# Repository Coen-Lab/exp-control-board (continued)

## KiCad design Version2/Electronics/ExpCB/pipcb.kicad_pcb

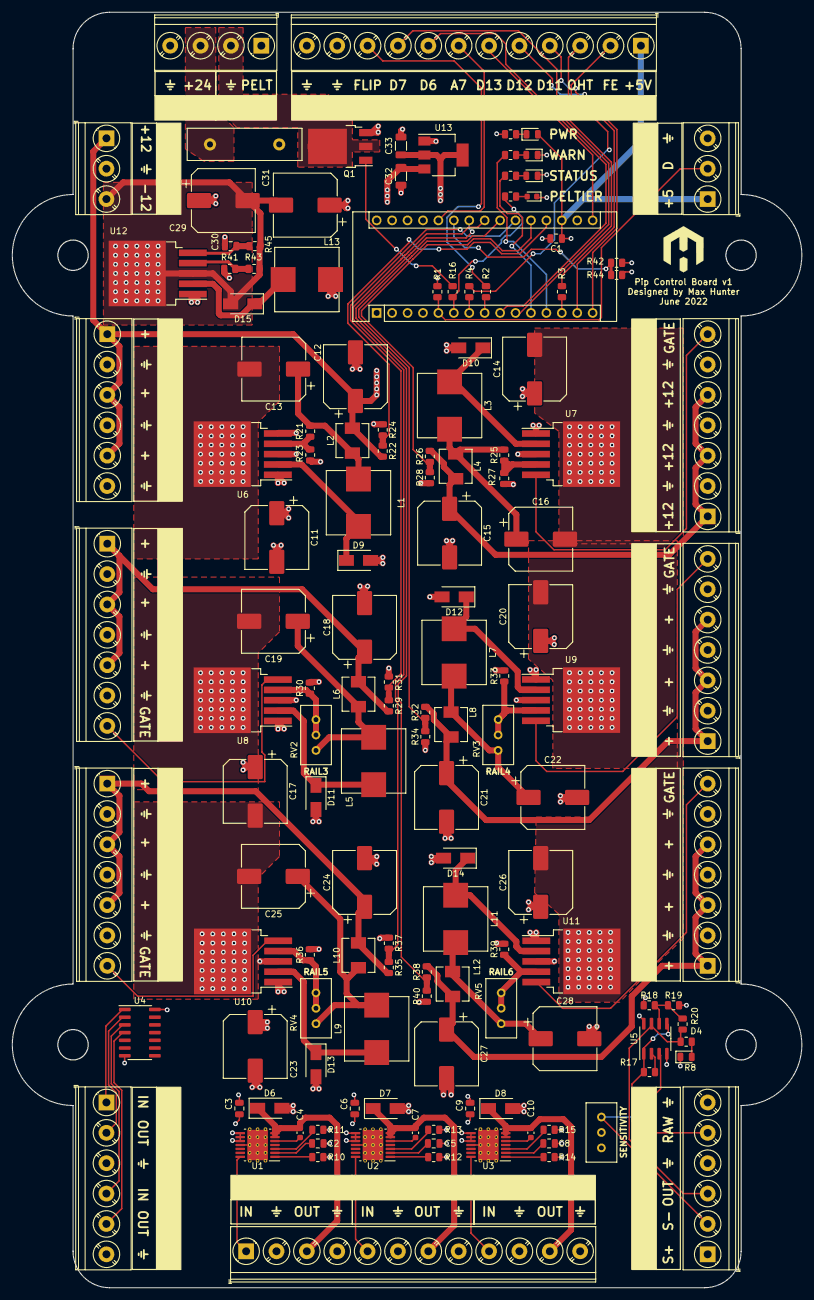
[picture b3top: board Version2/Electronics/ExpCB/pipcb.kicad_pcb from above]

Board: 4 copper layers, 130.0 x 210.0 mm, 140 parts (0 on the bottom side), 94 nets.

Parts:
A1: Arduino_Nano_v3.x; Arduino_Nano
C1, C30: 100n; C_0805_2012Metric
C2, C5, C8: 150n; C_0805_2012Metric
C3, C6, C9: 1u; C_0805_2012Metric
C4, C7, C10: 470p; C_0603_1608Metric
C11, C12, C13, C14, C15, C16, C17, C18, C19, C20, C21, C22, C23, C24, C25, C26, C27, C28, C29, C31: 220u; CP_Elec_10x10
C32, C33: 10u; C_1206_3216Metric
D1, D4: GREEN; LED_0805_2012Metric
D2: RED; LED_0805_2012Metric
D3: YELLOW; LED_0805_2012Metric
D5: BLUE; LED_0603_1608Metric
D6, D7, D8, D9, D10, D11, D12, D13, D14, D15: SS34; D_SMA
F1: 10A; Fuse_Littelfuse-LVR100
J1: 24V; TerminalBlock_Phoenix_PT-1,5-4-5.0-H_1x04_P5.00mm_Horizontal
J2: RAIL1; TerminalBlock_Phoenix_PT-1,5-6-5.0-H_1x06_P5.00mm_Horizontal
J3: RAIL2; TerminalBlock_Phoenix_PT-1,5-7-5.0-H_1x07_P5.00mm_Horizontal
J4: RAIL3; TerminalBlock_Phoenix_PT-1,5-7-5.0-H_1x07_P5.00mm_Horizontal
J5: RAIL4; TerminalBlock_Phoenix_PT-1,5-7-5.0-H_1x07_P5.00mm_Horizontal
J6: RAIL5; TerminalBlock_Phoenix_PT-1,5-7-5.0-H_1x07_P5.00mm_Horizontal
J7: RAIL6; TerminalBlock_Phoenix_PT-1,5-7-5.0-H_1x07_P5.00mm_Horizontal
J8: PHOTODIODE_PWR; TerminalBlock_Phoenix_PT-1,5-3-5.0-H_1x03_P5.00mm_Horizontal
J10: TEMP_SENSOR; TerminalBlock_Phoenix_PT-1,5-3-5.0-H_1x03_P5.00mm_Horizontal
J12: GPIO; TerminalBlock_Phoenix_PT-1,5-12-5.0-H_1x12_P5.00mm_Horizont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
J13: TTL INVERTERS; TerminalBlock_Phoenix_PT-1,5-6-5.0-H_1x06_P5.00mm_Horizontal
J14: PHOTOSENSOR; TerminalBlock_Phoenix_PT-1,5-6-5.0-H_1x06_P5.00mm_Horizontal
J15: VALVES; TerminalBlock_Phoenix_PT-1,5-12-5.0-H_1x12_P5.00mm_Horizont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
L1, L3, L5, L7, L9, L11, L13: 33uH 5A; PowerInductor_1004S
L2, L4, L6, L8, L10, L12: 3.3uH 5A; L_Sunlord_MWSA0518_5.4x5.2mm
Q1: VBE1410; TO-252-3_TabPin2
R1: 4.7k; R_0805_2012Metric
R2, R3, R4, R5, R6, R7, R16: 220R; R_0805_2012Metric
R8, R9: 1K; R_0805_2012Metric
R10, R12, R14: 120k; R_0805_2012Metric
R11, R13, R15: 200k; R_0805_2012Metric
R17: 10K; R_0805_2012Metric
R18, R19: 30k; R_0805_2012Metric
R20: 150k; R_0805_2012Metric
R21, R24, R25, R28, R31, R34, R37, R40, R41, R44: 8.87k 1%; R_0805_2012Metric
R22, R26, R29, R32, R35, R38, R42: 47k 1%; R_0805_2012Metric
R23, R27, R43: 1k 1%; R_0805_2012Metric
R30, R33, R36, R39: 2k; R_0805_2012Metric
R45: 47k; R_0805_2012Metric
RV1: 10M; Potentiometer_Bourns_3296W_Vertical
RV2, RV3, RV4, RV5: 47k 10-turn; Potentiometer_Bourns_3296W_Vertical
U1, U2, U3: DRV104; HTSSOP-14-1EP_4.4x5mm_P0.65mm_EP3.4x5mm_Mask3x3.1mm_Thermal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
U4: 74HC14; SOIC-14_3.9x8.7mm_P1.27mm
U5: MCP6002-xSN; SOIC-8_3.9x4.9mm_P1.27mm
U6, U7, U8, U9, U10, U11, U12: LM2596S-ADJ; TO-263-5_TabPin3
U13: AMS1117-5.0; SOT-223-3_TabPin2

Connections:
24_V_ADC: A1.25 (A6), R42.1, R44.2
+24V: C11.1, C14.1, C17.1, C20.1, C23.1, C26.1, C29.1, C30.1, F1.2, J1.1, R42.2, U6.1 (VIN), U7.1 (VIN), U8.1 (VIN), U9.1 (VIN), U10.1 (VIN), U11.1 (VIN), U12.1 (VIN)
-12V: C29.2, C31.2, D15.2 (A), J8.3, R43.2, R45.2, U12.3 (GND)
FLIPPER_ENABLE: A1.7 (D4), R4.2
FLIPPER_OUT: A1.8 (D5), R2.2
GND: A1.4 (GND), A1.29 (GND), C1.2, C2.2, C3.2, C5.2, C6.2, C8.2, C9.2, C11.2, C12.2, C13.2, C14.2, C15.2, C16.2, C17.2, C18.2, C19.2, C20.2, C21.2, C22.2, C23.2, C24.2, C25.2, C26.2, C27.2, C28.2, C31.1, C32.2, C33.2, D2.1 (K), D3.1 (K), D4.1 (K), D5.1 (K), D6.2 (A), D7.2 (A), D8.2 (A), D9.2 (A), D10.2 (A), D11.2 (A), D12.2 (A), D13.2 (A), D14.2 (A), J1.4, J2.2, J2.4, J2.6, J3.2, J3.4, J3.6, J4.2, J4.4, J4.6, J5.2, J5.4, J5.6, J6.2, J6.4, J6.6, J7.2, J7.4, J7.6, J8.2, J10.3, J12.11, J12.12, J13.3, J13.6, J14.4, J14.6, J15.2, J15.4, J15.6, J15.8, J15.10, J15.12, L13.2, Q1.3 (S), R5.1, R10.2, R11.2, R12.2, R13.2, R14.2, R15.2, R19.2, R23.2, R24.1, R27.2, R28.1, R30.2, R31.1, R33.2, R34.1, R36.2, R37.1, R39.2, R40.1, R41.2, R44.1, RV1.2, RV1.3, U1.11 (GND), U1.15 (PPAD), U2.11 (GND), U2.15 (PPAD), U3.11 (GND), U3.15 (PPAD), U4.7 (GND), U5.4 (V-), U6.3 (GND), U6.5 (~ON/OFF), U7.3 (GND), U8.3 (GND), U9.3 (GND), U10.3 (GND), U11.3 (GND), U13.1 (GND)
GPIO1: A1.14 (D11), J12.4
GPIO2: A1.15 (D12), J12.5
GPIO3: A1.16 (D13), J12.6
GPIO4: A1.26 (A7), J12.7
GPIO5: A1.9 (D6), J12.8
GPIO6: A1.10 (D7), J12.9
INV_1_IN: J13.1, U4.1
INV_1_OUT: J13.2, U4.2
INV_2_IN: J13.4, U4.3
INV_2_OUT: J13.5, U4.4
LED_STATUS: A1.11 (D8), R7.2
LED_WARNING: A1.12 (D9), R6.2
unnamed: C2.1, U1.2 (DELAY_ADJ)
unnamed: C4.2, U1.5 (BOOT)
unnamed: C5.1, U2.2 (DELAY_ADJ)
unnamed: C7.2, U2.5 (BOOT)
unnamed: C8.1, U3.2 (DELAY_ADJ)
unnamed: C10.2, U3.5 (BOOT)
unnamed: C13.1, L1.2, L2.1, R21.2
unnamed: C16.1, L3.2, L4.1, R25.2
unnamed: C19.1, L5.2, L6.1, RV2.3
unnamed: C22.1, L7.2, L8.1, RV3.3
unnamed: C25.1, L9.2, L10.1, RV4.3
unnamed: C28.1, L11.2, L12.1, RV5.3
unnamed: C30.2, R45.1, U12.5 (~ON/OFF)
unnamed: D1.1 (K), R5.2
unnamed: D2.2 (A), R6.1
unnamed: D3.2 (A), R7.1
unnamed: D4.2 (A), R8.1
unnamed: D5.2 (A), R9.1
unnamed: D9.1 (K), L1.1, U6.2 (OUT)
unnamed: D10.1 (K), L3.1, U7.2 (OUT)
unnamed: D11.1 (K), L5.1, U8.2 (OUT)
unnamed: D12.1 (K), L7.1, U9.2 (OUT)
unnamed: D13.1 (K), L9.1, U10.2 (OUT)
unnamed: D14.1 (K), L11.1, U11.2 (OUT)
unnamed: D15.1 (K), L13.1, U12.2 (OUT)
unnamed: F1.1, J1.3
unnamed: J12.2, R4.1
unnamed: J12.3, R3.1
unnamed: J12.10, R2.1
unnamed: Q1.1 (G), R16.1
unnamed: R10.1, U1.1 (DUTY_ADJ)
unnamed: R11.1, U1.3 (OSC_ADJ)
unnamed: R12.1, U2.1 (DUTY_ADJ)
unnamed: R13.1, U2.3 (OSC_ADJ)
unnamed: R14.1, U3.1 (DUTY_ADJ)
unnamed: R15.1, U3.3 (OSC_ADJ)
unnamed: R17.2, U5.2 (-)
unnamed: R18.2, R19.1, R20.2, U5.6 (-)
unnamed: R21.1, R23.1, U6.4 (FB)
unnamed: R25.1, R27.1, U7.4 (FB)
unnamed: R30.1, RV2.1, RV2.2, U8.4 (FB)
unnamed: R33.1, RV3.1, RV3.2, U9.4 (FB)
unnamed: R36.1, RV4.1, RV4.2, U10.4 (FB)
unnamed: R39.1, RV5.1, RV5.2, U11.4 (FB)
unnamed: R41.1, R43.1, U12.4 (FB)
OVERHEAT: A1.13 (D10), R3.2
PELTIER_CONTROL: A1.6 (D3), R9.2, R16.2
PELTIER_OUT: J1.2, Q1.2 (D)
PS_1: A1.18 (AREF), A1.27 (+5V), C1.1, C33.1, D1.2 (A), J10.1, J12.1, J14.1, R1.1, R18.1, U4.14 (VCC), U5.8 (V+), U13.2 (VO)
PS_2: J14.2, RV1.1, U5.3 (+)
PS_RAW_OUT: J14.5, R17.1, U5.1, U5.5 (+)
PS_TRIGGER: J14.3, R8.2, R20.1, U5.7
RAIL1+: C3.1, C6.1, C9.1, C12.1, C32.1, J2.1, J2.3, J2.5, J8.1, L2.2, R22.2, U1.8 (VPS1), U1.9 (VPS2), U1.10 (+VS), U2.8 (VPS1), U2.9 (VPS2), U2.10 (+VS), U3.8 (VPS1), U3.9 (VPS2), U3.10 (+VS), U13.3 (VI)
RAIL1_V_ADC: A1.19 (A0), R22.1, R24.2
RAIL2+: C15.1, J3.1, J3.3, J3.5, L4.2, R26.2
RAIL2_GATE: J3.7, U7.5 (~ON/OFF)
RAIL2_V_ADC: A1.20 (A1), R26.1, R28.2
RAIL3+: C18.1, J4.1, J4.3, J4.5, L6.2, R29.2
RAIL3_GATE: J4.7, U8.5 (~ON/OFF)
RAIL3_V_ADC: A1.21 (A2), R29.1, R31.2
RAIL4+: C21.1, J5.1, J5.3, J5.5, L8.2, R32.2
RAIL4_GATE: J5.7, U9.5 (~ON/OFF)
RAIL4_V_ADC: A1.22 (A3), R32.1, R34.2
RAIL5+: C24.1, J6.1, J6.3, J6.5, L10.2, R35.2
RAIL5_GATE: J6.7, U10.5 (~ON/OFF)
RAIL5_V_ADC: A1.23 (A4), R35.1, R37.2
RAIL6+: C27.1, J7.1, J7.3, J7.5, L12.2, R38.2
RAIL6_GATE: J7.7, U11.5 (~ON/OFF)
RAIL6_V_ADC: A1.24 (A5), R38.1, R40.2
TEMP_SENSOR: A1.5 (D2), J10.2, R1.2
VALVE1_IN: J15.1, U1.14 (INPUT)
VALVE1_OUT: C4.1, D6.1 (K), J15.3, U1.6 (OUT1), U1.7 (OUT2)
VALVE2_IN: J15.5, U2.14 (INPUT)
VALVE2_OUT: C7.1, D7.1 (K), J15.7, U2.6 (OUT1), U2.7 (OUT2)
VALVE3_IN: J15.9, U3.14 (INPUT)
VALVE3_OUT: C10.1, D8.1 (K), J15.11, U3.6 (OUT1), U3.7 (OUT2)

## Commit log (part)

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2023-11-08 File renaming
2024-02-18 Added v2 and v3 PCB design files
2024-03-25 Updated main page with hyperlinks
2024-03-25 Add docs
2024-03-25 Fixed documentation errors
2024-04-25 Moving files
2024-04-25 MovingFiles
2024-04-26 Update for case
2024-04-26 Case > Enclosure
2024-10-21 Add files via upload
    Added V3 Firmware
